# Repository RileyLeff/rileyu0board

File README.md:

# Riley U0 Board

This is a hello world project in kicad. Just learning my way around.

Attempting to design a little board for a STM32U0 MCU.

Down the road (maybe a long time from now) I'd like to develop some open-source hardware projects as cheaper, more tractable alternatives to commercial scientific tools. I have a suspicion that the hobbyist electronics market is a severely under-utilized asset in ecological research.

If I'm able to come up with something useful here, I'll flesh out the docs and write a BSP in rust. But highly likely that I get 3/4 of the way done with this and feel like i've learned enough to move on to designing a non-toy project. We'll see.

## Current Status

I went in there and connected a bunch of stuff incorrectly. Hell yeah.

I think next steps for me are 1.) figuring out library management, then 2.) making an extremely barebones breakout for just the MCU and perhaps a separately-broken-out USB connector. Would probably be instructive for me to breadboard up the oscillator, ADC, USB, etc connections by hand and confirming i understand how they work before yeeting them off into the JLCPCB abyss for manufacture.

## Stuff Riley Needs To Figure Out

- it would be nice to have a precommit that generates a new .pdf of the schematic every time i commit
- is it possible to run a design rules check on precommit/CI?
- Library/footprint management oh my god
- What the hell am i supposed to do with analog signals regarding EMI/noise stuff? e.g. especially with regards to amplifying analog signals to go into ADC
- Get lowpowerpilled: how much does underclocking/undervolting help?
- if i have some peripheral device e.g. i2c sensor where quiescent power consumption is much higher than my idle MCU, how can i cut off consumption when i'm not using it?
- I have legitimately no idea how oscillators work and i need pretty accurate time for my projects

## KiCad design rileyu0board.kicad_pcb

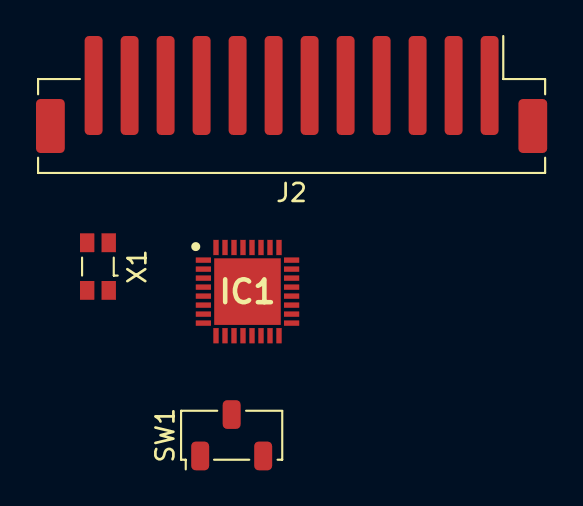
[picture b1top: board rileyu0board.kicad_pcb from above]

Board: 2 copper layers, 4 parts (0 on the bottom side), 17 nets, no tracks yet.

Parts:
IC1: STM32U073KCU3; QFN50P500X500X60-33N-D
J2: Conn_01x12_Pin; JST_PH_B12B-PH-SM4-TB_1x12-1MP_P2.00mm_Vertical
SW1: SW_Nidec_CAS-120A1; Nidec_Copal_CAS-120A
X1: SG-3030CM; Oscillator_SMD_SeikoEpson_SG3030CM

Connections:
+3V3: IC1.1 (VDD), SW1.1 (C)
GND: IC1.16 (VSS_1), IC1.32 (VSS_2), IC1.33 (EP), SW1.3 (A), X1.2 (GND)
unnamed: IC1.20 (PA10), J2.1
unnamed: IC1.21 (PA11_[PA9]), J2.2
unnamed: IC1.22 (PA12_[PA10]), J2.3
unnamed: IC1.23 (PA13), J2.4
unnamed: IC1.24 (PA14), J2.5
unnamed: IC1.25 (PA15), J2.6
unnamed: IC1.26 (PB3), J2.7
unnamed: IC1.27 (PB4), J2.8
unnamed: IC1.28 (PB5), J2.9
unnamed: IC1.29 (PB6), J2.10
unnamed: IC1.30 (PB7), J2.11
unnamed: IC1.2 (PC14-OSC32_IN), X1.4 (Vcc)
unnamed: IC1.3 (PC15-OSC32_OUT), X1.1 (VIO)
unnamed: IC1.4 (PF2-NRST), SW1.2 (B)
unnamed: IC1.31 (PF3-BOOT0), J2.12

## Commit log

2024-10-11 init commit
2024-10-11 readme
2024-10-11 jesus i am confused about footprints
2024-10-11 learning
2024-10-11 everything is wrong but stuff is happening
